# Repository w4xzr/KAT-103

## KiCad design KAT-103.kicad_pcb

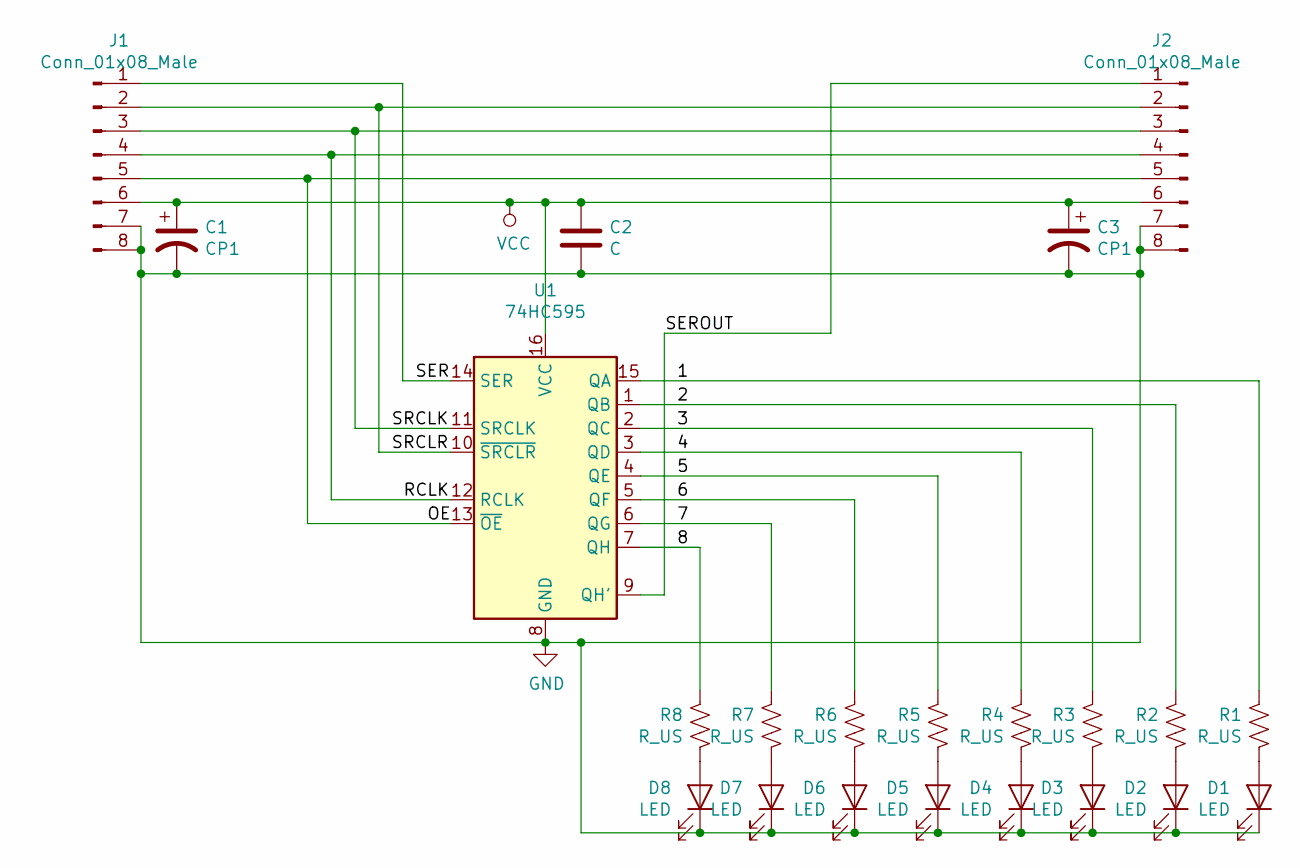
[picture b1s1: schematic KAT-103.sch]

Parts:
C1, C3: CP1; CP_Radial_D5.0mm_P2.00mm
C2: C; C_Rect_L7.0mm_W2.5mm_P5.00mm
D1, D2, D3, D4, D5, D6, D7, D8: LED; LED_D5.0mm
J1, J2: Conn_01x08_Male; PinHeader_1x08_P2.54mm_Vertical
R1, R2, R3, R4, R5, R6, R7, R8: R_US; R_Axial_DIN0207_L6.3mm_D2.5mm_P10.16mm_Horizontal
U1: 74HC595; DIP-16_W7.62mm

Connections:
/1: R1.1, U1.15 (QA)
/2: R2.1, U1.1 (QB)
/3: R3.1, U1.2 (QC)
/4: R4.1, U1.3 (QD)
/5: R5.1, U1.4 (QE)
/6: R6.1, U1.5 (QF)
/7: R7.1, U1.6 (QG)
/8: R8.1, U1.7 (QH)
/OE: J1.5, J2.5, U1.13 (~OE)
/RCLK: J1.4, J2.4, U1.12 (RCLK)
/SER: J1.1, U1.14 (SER)
/SEROUT: J2.1, U1.9 (QH')
/SRCLK: J1.3, J2.3, U1.11 (SRCLK)
/SRCLR: J1.2, J2.2, U1.10 (~SRCLR)
GND: C1.2, C2.2, C3.2, D1.1 (K), D2.1 (K), D3.1 (K), D4.1 (K), D5.1 (K), D6.1 (K), D7.1 (K), D8.1 (K), J1.7, J1.8, J2.7, J2.8, U1.8 (GND)
unnamed: D1.2 (A), R1.2
unnamed: D2.2 (A), R2.2
unnamed: D3.2 (A), R3.2
unnamed: D4.2 (A), R4.2
unnamed: D5.2 (A), R5.2
unnamed: D6.2 (A), R6.2
unnamed: D7.2 (A), R7.2
unnamed: D8.2 (A), R8.2
VCC: C1.1, C2.1, C3.1, J1.6, J2.6, U1.16 (VCC)

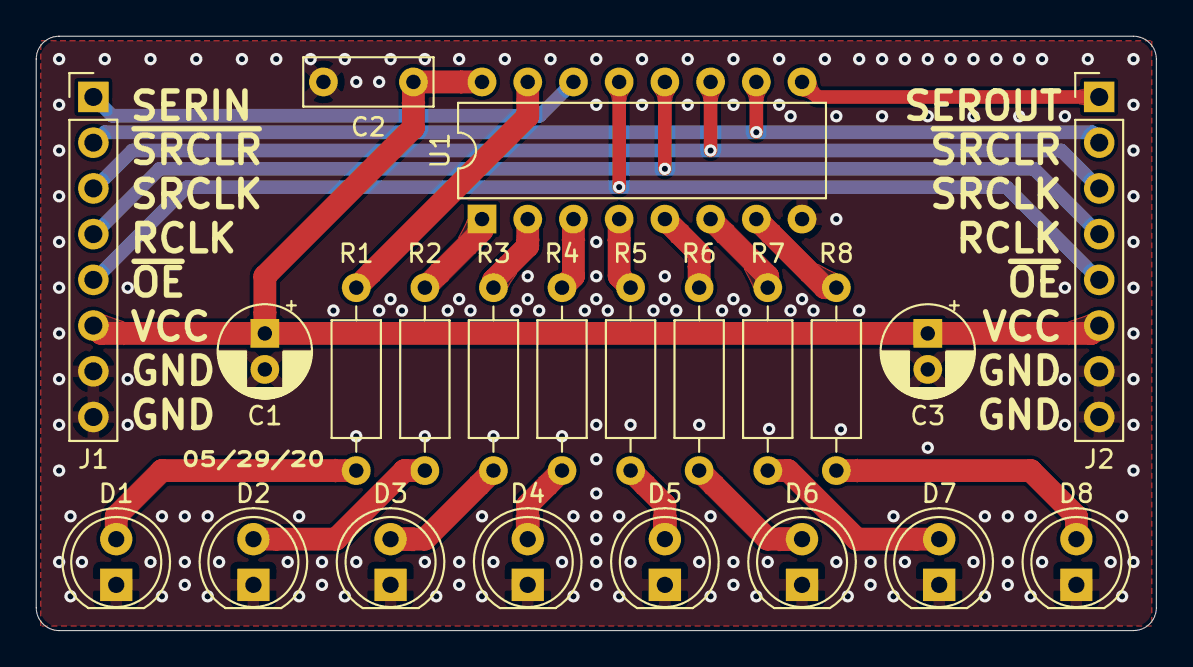
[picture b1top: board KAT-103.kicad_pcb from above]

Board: 2 copper layers, 62.2 x 33.0 mm, 22 parts (0 on the bottom side), 24 nets.

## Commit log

2020-07-03 init
2020-07-03 Added README.md
2020-07-04 Updated Images: Sat Jul 4 00:01:37 UTC 2020 (Build 2)
    [skip ci]
2020-07-04 [ImgBot] Optimize images
    *Total -- 736.63kb -> 519.70kb (29.45%)
    /Images/Back.png -- 290.08kb -> 201.32kb (30.6%)
    /Images/Front.png -- 446.55kb -> 318.39kb (28.7%)
2020-07-04 Cleanup
2020-07-04 Updated Images: Sat Jul 4 00:31:31 UTC 2020 (Build 6)
    [skip ci]
